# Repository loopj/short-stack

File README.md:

<div align="center">
  <h1>

  </h1>

  <h4>World's Smallest Nintendo Wii, using a trimmed motherboard and custom stacked PCBs</h4>

  <p>
    <a href="#features">Features</a> &middot;
    <a href="#size--scale">Size & Scale</a> &middot;
    <a href="#components">Components</a> &middot;
    <a href="#build-guide">Build Guide</a> &middot;
    <a href="#special-thanks">Special Thanks</a>
  </p>
</div>

## Features

- World's smallest "to scale" Wii console
- Powered by USB-C
- HDMI for lossless digital audio and video (powered by [GCVideo](https://github.com/ikorb/gcvideo))
- Bluetooth for Wii remotes and accessories
- MicroSD card stores games and saves, instead of disc drive & memory cards
- 4 GameCube controller ports
- Power, reset, and sync buttons
- Power indicator LED and iconic blue glowing disc slot
- Soft shutdown, power on/off via Wiimote

## Size & Scale

This is a **1:2.38 scale** model of an original Nintendo Wii console, but since that is hard to visualize here are some other stats:

- Same size as a typical deck of playing cards
- **7.4% the volume** of an original Wii console
- You could fit **13.5** of these inside an original Wii

I'm pretty sure this sets the record for the smallest functional scale-model Wii console, but let me know if I'm wrong!

### Could we go smaller?

Yes! It is definitely possible to go smaller than this. My [version of the Omega trim](images/trim.png) keeps all four main mounting holes, which makes it around 7mm wider than a classic Omega trim. Additionally [Wesk](https://twitter.com/Weskmods) has managed to get a Wii motherboard down to 52x52mm on his final destination trim, which is a a full 10mm narrower than my trim. I estimate you could reduce the volume by a further 25-30% without losing any functionality, but it would be an incredibly tight fit and tricky to assemble.

## Components

As the name implies, *Short Stack* is built from a stack of custom PCBs, and a custom heatsink, that are all designed to fit together in a compact and modular way.

### A modular motherboard

Making a tiny build like this is made possible by trimming the Wii motherboard down to the bare essentials. The result is a board which is just *62x62mm*, but still contains the CPU, GPU, RAM and flash memory.

Since we removed the original power circuitry and trimmed off the USB, Bluetooth, and GameCube connectors, we need to provide power and data to the board another way. I designed a couple of boards which solder directly to the front of a trimmed Wii motherboard to provide power and data, which help avoid a tangled mess of wires.

The [Wii Power Strip](https://github.com/loopj/wii-power-strip) supplies power to the Wii motherboards using a Molex Pico-Lock connector, and additionally has footprints to help relocate of a couple of capacitors which are typically removed when trimming a Wii.

[Periphlex](https://github.com/loopj/periphlex) is a flex PCB which breaks out the Bluetooth, USB and GameCube controller data lines, as well as the power, shutdown, and reset GPIOs. These are then made available via a 14-pin FFC connector. This approach replaces 11 magnet wires with a single, removable ribbon cable.

On the back of the motherboard, I'm using two open-source boards designed by the very talented [YveltalGriffin](https://github.com/mackieks). [fujiflex](https://github.com/mackieks/fujiflex) provides digital A/V output using GCVideo, and [nandFlex](https://github.com/mackieks/nandFlex) relocates the Wii's NAND memory chip, to enable the tight trim.

### Custom PCBs

In addition to the modular boards on the motherboard, I designed two PCBs specific to Short Stack which provide the rest of the functionality for the console.

The *main board* PCB hosts the power regulators, USB to microSD logic, HDMI connector, GameCube ports, and a microcontroller for power management. A 14-pin ribbon cable connects this board to the Wii motherboard via *Periphlex*, and a power cable delivers power to the *Power Strip*.

The *front panel* PCB hosts the power, reset, and sync buttons, as well as the power LED and disc slot LEDs. This board connects to the main board via a short 8-pin ribbon cable.

Since the GameCube controller connectors on the original Wii wouldn't fit cleanly on a build of this size, I use TRRS headphone connectors instead. This is the exact same approach used on the amazing [GC Nano](https://bitbuilt.net/forums/index.php?threads/gc-nano-the-worlds-smallest-gamecube.5697/) and in fact I made sure the dongles are pinout compatible!

### Cooling

The final part of the "stack" is a custom heatsink which is designed to be as low profile as possible, while still providing adequate cooling for the Wii's CPU and GPU. The heatsink is designed to be machined from aluminum or copper, and incorporates mounting holes which align with those on the Wii motherboard.

I managed to find a tiny 5V blower fan ([Pelonis AGB208N](https://catalog.pelonistechnologies.com/item/air-g-series-micro-fans-and-micro-blowers/micro-fans-and-micro-blowers/agb208n)) which measures just 20x20x8mm and somehow puts out 0.84 CFM of air. This blows air through the heatsink fins, out the side of the case.

### Case

The stack is housed in a custom 3D printed case, secured with four M2.5 screws and spacers. The rest of case is assembled using self-tapping M1.2 screws. The screw locations and fan vents are positioned to match the original Wii case as closely as possible, to minimize visible screws.

You can access files on the SD card by connecting the console to a computer via USB, but I also included an access panel on the front of the case where the original Wii SD card slot is found. This panel is held in place by magnets and can be removed to access the SD card without opening the case. Shout out to Wesk for the magnet idea!

To keep the clean aesthetic of the original Wii I wanted to hide the GameCube controller ports behind a panel. I always hated the hinged design of the original, and it is quite difficult to replicate at this scale, so I redesigned this panel to be a sliding panel.

The Wii's iconic disc slot lights are recreated using a 1.5mm thick custom cut acrylic light diffuser, which is illuminated by two side-mounted addressable LEDs on the front panel board. The power, reset, and sync buttons are all also 3D printed, and the power button hosts a tiny light pipe to allow the power LED to shine through.

I FDM printed the case on a Voron 2.4 in ABS using a 0.4mm nozzle at 0.1mm layer height, but it should print fine in PLA or PETG on a well-tuned printer. At this scale, dimensional accuracy is important. In theory it should be possible to print this on an SLA printer, but I haven't tried it.

## Build Guide

> [!CAUTION]
> This is not a beginner project! This build requires performing a challenging motherboard trim, fine pitch soldering, and PCB assembly. If you are not comfortable with these tasks, I would recommend starting with a simpler project and working your way up - check out the [BitBuilt forums](https://bitbuilt.net) for some awesome project worklogs.

### What you'll need

- 4-layer Wii motherboard
- [nandFlex](https://github.com/mackieks/nandFlex) board (or [4Layer Technologies RVL-NAND](https://4layertech.com/products/rvl-nand-flex-board-pack-of-2))
- Assembled [fujiflex](https://github.com/mackieks/fujiflex) (or [ElectronAVE](https://electron-shepherd.com/products/electronave-kit))
- Assembled [Wii Power Strip](https://github.com/loopj/wii-power-strip/tree/r1) - **must be revision 1!**
- Assembled [Periphlex](https://github.com/loopj/periphlex)
- [Short Stack main board](main-board/KiCad) - 1.2mm thickness, stencil recommended
- [Short Stack front panel](front-panel/KiCad) - 0.8mm thickness, black soldermask, stencil recommended
- [Heatsink](case/heatsink.step) - machined from aluminum or copper
- [Light diffuser](case/disc-light-diffuser.dxf) - cut from 1.5mm thick acrylic
- The components and hardware from the [bill of materials](full-bom.xlsx)

### Assembly

- Assemble main board and front panel PCBs
  - I recommend using a solder stencil and a hot plate or reflow oven
  - If using a hot plate, hand solder the headphone connectors after reflowing the rest of the components
  - Secure two 3 x 1mm magnets inside the holes on the front panel board using a dab of CA glue
- Flash the [main board firmware](main-board/firmware)
- Prepare and trim the Wii motherboard
  - Relocate the NAND, test it still boots
  - Perform a wireless U10 relocation, test it still boots - you may wish to wire a magnet wire to the [`SHUTDOWN` via](https://bitbuilt.net/forums/index.php?threads/soft-shutdown-power-on-via-bluetooth.6239/) first
  - Install fujiflex, and test digital A/V output works
  - Trim the motherboard (see [trim dimensions](images/trim.png))
- Assemble and install *Power Strip* ([see instructions](https://github.com/loopj/wii-power-strip/tree/r1#installation))
- Assemble and install *Periphlex* ([see instructions](https://github.com/loopj/periphlex#installation))
- Connect the boards
  - Connect the main board to the motherboard via a 14-pin FFC cable to *Periphlex*
  - Connect the main board to the motherboard via a 5-pin Molex Pico-Lock cable to *Power Strip*
  - Connect the front panel board to the main board via an 8-pin FFC cable
  - Connect the fan to the main board
  - Apply thermal paste to the CPU and GPU
  - Stack the components: heatsink, motherboard, M2.5 x 3mm spacers, main board
  - Install the stack to the case bottom using M2.5 x 12mm wafer head screws
- Secure the top of the case to the bottom using four M1.2 x 4mm screws
- Secure the front panel PCB to the front of the case using two M1.2 x 3mm screws
- Secure the front of the case to the bottom of the case using two M1.2 x 4mm screws
- Press-fit two 3 x 1mm magnets into the holes on the sd card cover, make sure they match polarity with the magnets on the front panel PCB
- Slide the side panel into the case

## Special Thanks

This project would not be possible without the amazing [BitBuilt community](https://bitbuilt.net), I'm truly standing on the shoulders of giants here.

In particular, I'd like to thank:

- [Wesk](https://twitter.com/Weskmods) for setting the bar so high with renders, for the suggestion of using magnets in the case assembly, and for the inspirational GC Nano
- [Aurelio](https://twitter.com/aureliomannara) for pointing me in the right direction to help figure the soft shutdown and power on via Wiimote.
- [YveltalGriffin](https://twitter.com/YveltalGriffin) for PCB design feedback, helping me when I was documenting the bluetooth module, and of course for fujiflex and nandFlex
- [CrazyGadget](https://twitter.com/crazygadgetmods) for helping me fix my GL823K on the first revision of my boards, and for the inspirational GC Nano
- [Y2K](https://twitter.com/y2k_x38) and supertazon for joining the PCB assembly live stream and being super supportive

## License

Permissively released under the Solderpad Hardware License v2.1

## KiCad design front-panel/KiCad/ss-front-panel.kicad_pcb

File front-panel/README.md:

# Short Stack Front Panel

This folder contains the KiCad schematic and PCB layout for the Short Stack front panel PCB.

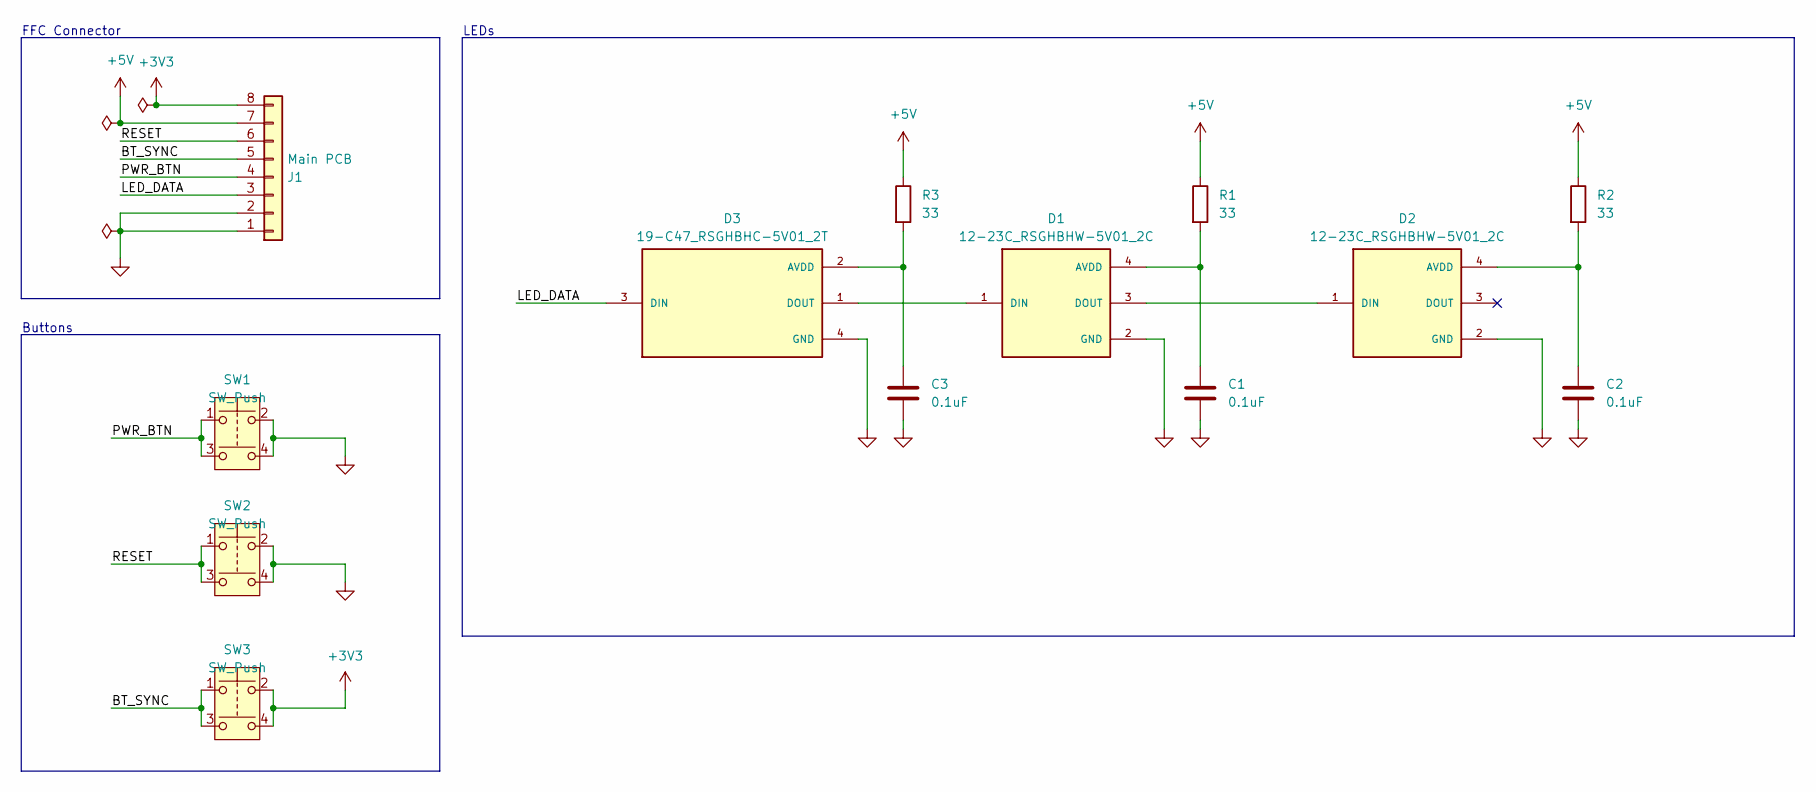
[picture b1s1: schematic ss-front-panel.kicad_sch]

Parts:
C1, C2, C3: 0.1uF; C_0402_1005Metric
D1, D2: 12-23C_RSGHBHW-5V01_2C; LED_12-23C_RSGHBHW-5V01_2C; MPN 12-23C/RSGHBHW-5V01/2C; Digi-Key Part # 1080-1624-1-ND
D3: 19-C47_RSGHBHC-5V01_2T; LED_19-C47_RSGHBHC-5V01_2T; MPN 19-C47/RSGHBHC-5V01/2T; Digi-Key Part # 1080-1623-1-ND
J1: Main PCB; 5034800800; MPN 5014610891; Digi-Key Part # WM14413CT-ND
R1, R2, R3: 33; R_0402_1005Metric
SW1, SW2, SW3: SW_Push; R668048; MPN R-668048; Digi-Key Part # 2508-R-668048CT-ND

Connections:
+3V3: J1.8, SW3.2, SW3.4
+5V: J1.7, R1.1, R2.1, R3.1
/BT_SYNC: J1.5, SW3.1, SW3.3
/LED_DATA: D3.3 (DIN), J1.3
/PWR_BTN: J1.4, SW1.1, SW1.3
/RESET: J1.6, SW2.1, SW2.3
GND: C1.2, C2.2, C3.2, D1.2 (GND), D2.2 (GND), D3.4 (GND), J1.1, J1.2, SW1.2, SW1.4, SW2.2, SW2.4
unnamed: C1.1, D1.4 (AVDD), R1.2
unnamed: D1.1 (DIN), D3.1 (DOUT)
unnamed: D1.3 (DOUT), D2.1 (DIN)
unnamed: C2.1, D2.4 (AVDD), R2.2
unnamed: C3.1, D3.2 (AVDD), R3.2

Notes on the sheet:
FFC Connector
Buttons
LEDs

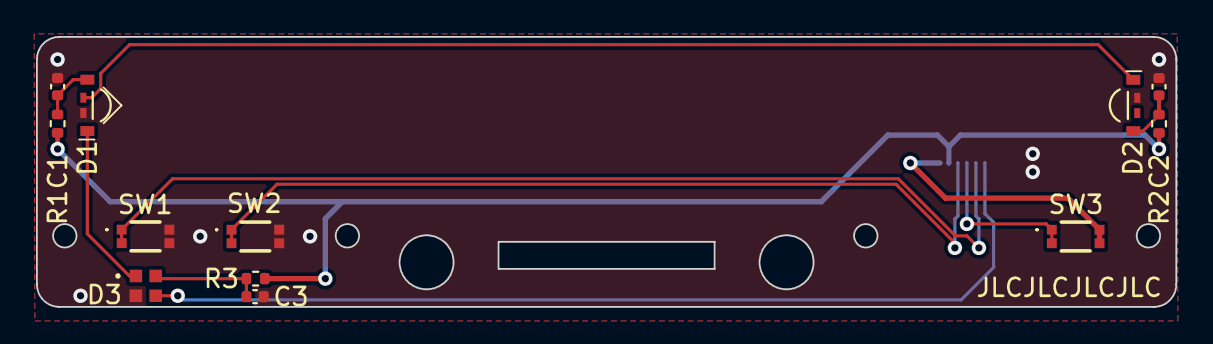
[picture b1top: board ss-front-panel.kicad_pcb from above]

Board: 2 copper layers, 63.3 x 15.0 mm, 13 parts (1 on the bottom side), 12 nets.

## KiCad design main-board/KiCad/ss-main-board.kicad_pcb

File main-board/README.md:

# Short Stack Main Board

The folder contains the KiCad schematic, pcb layouts, and firmware for the Short Stack main PCB.

## Future enhancements

- [ ] Dual load switch per GC line to allow hotplug (TPS22960 or similar)
- [ ] Potentially drop the 5V load switch if we are load switching each GC controller
- [ ] Hang bluetooth antenna off right edge of board

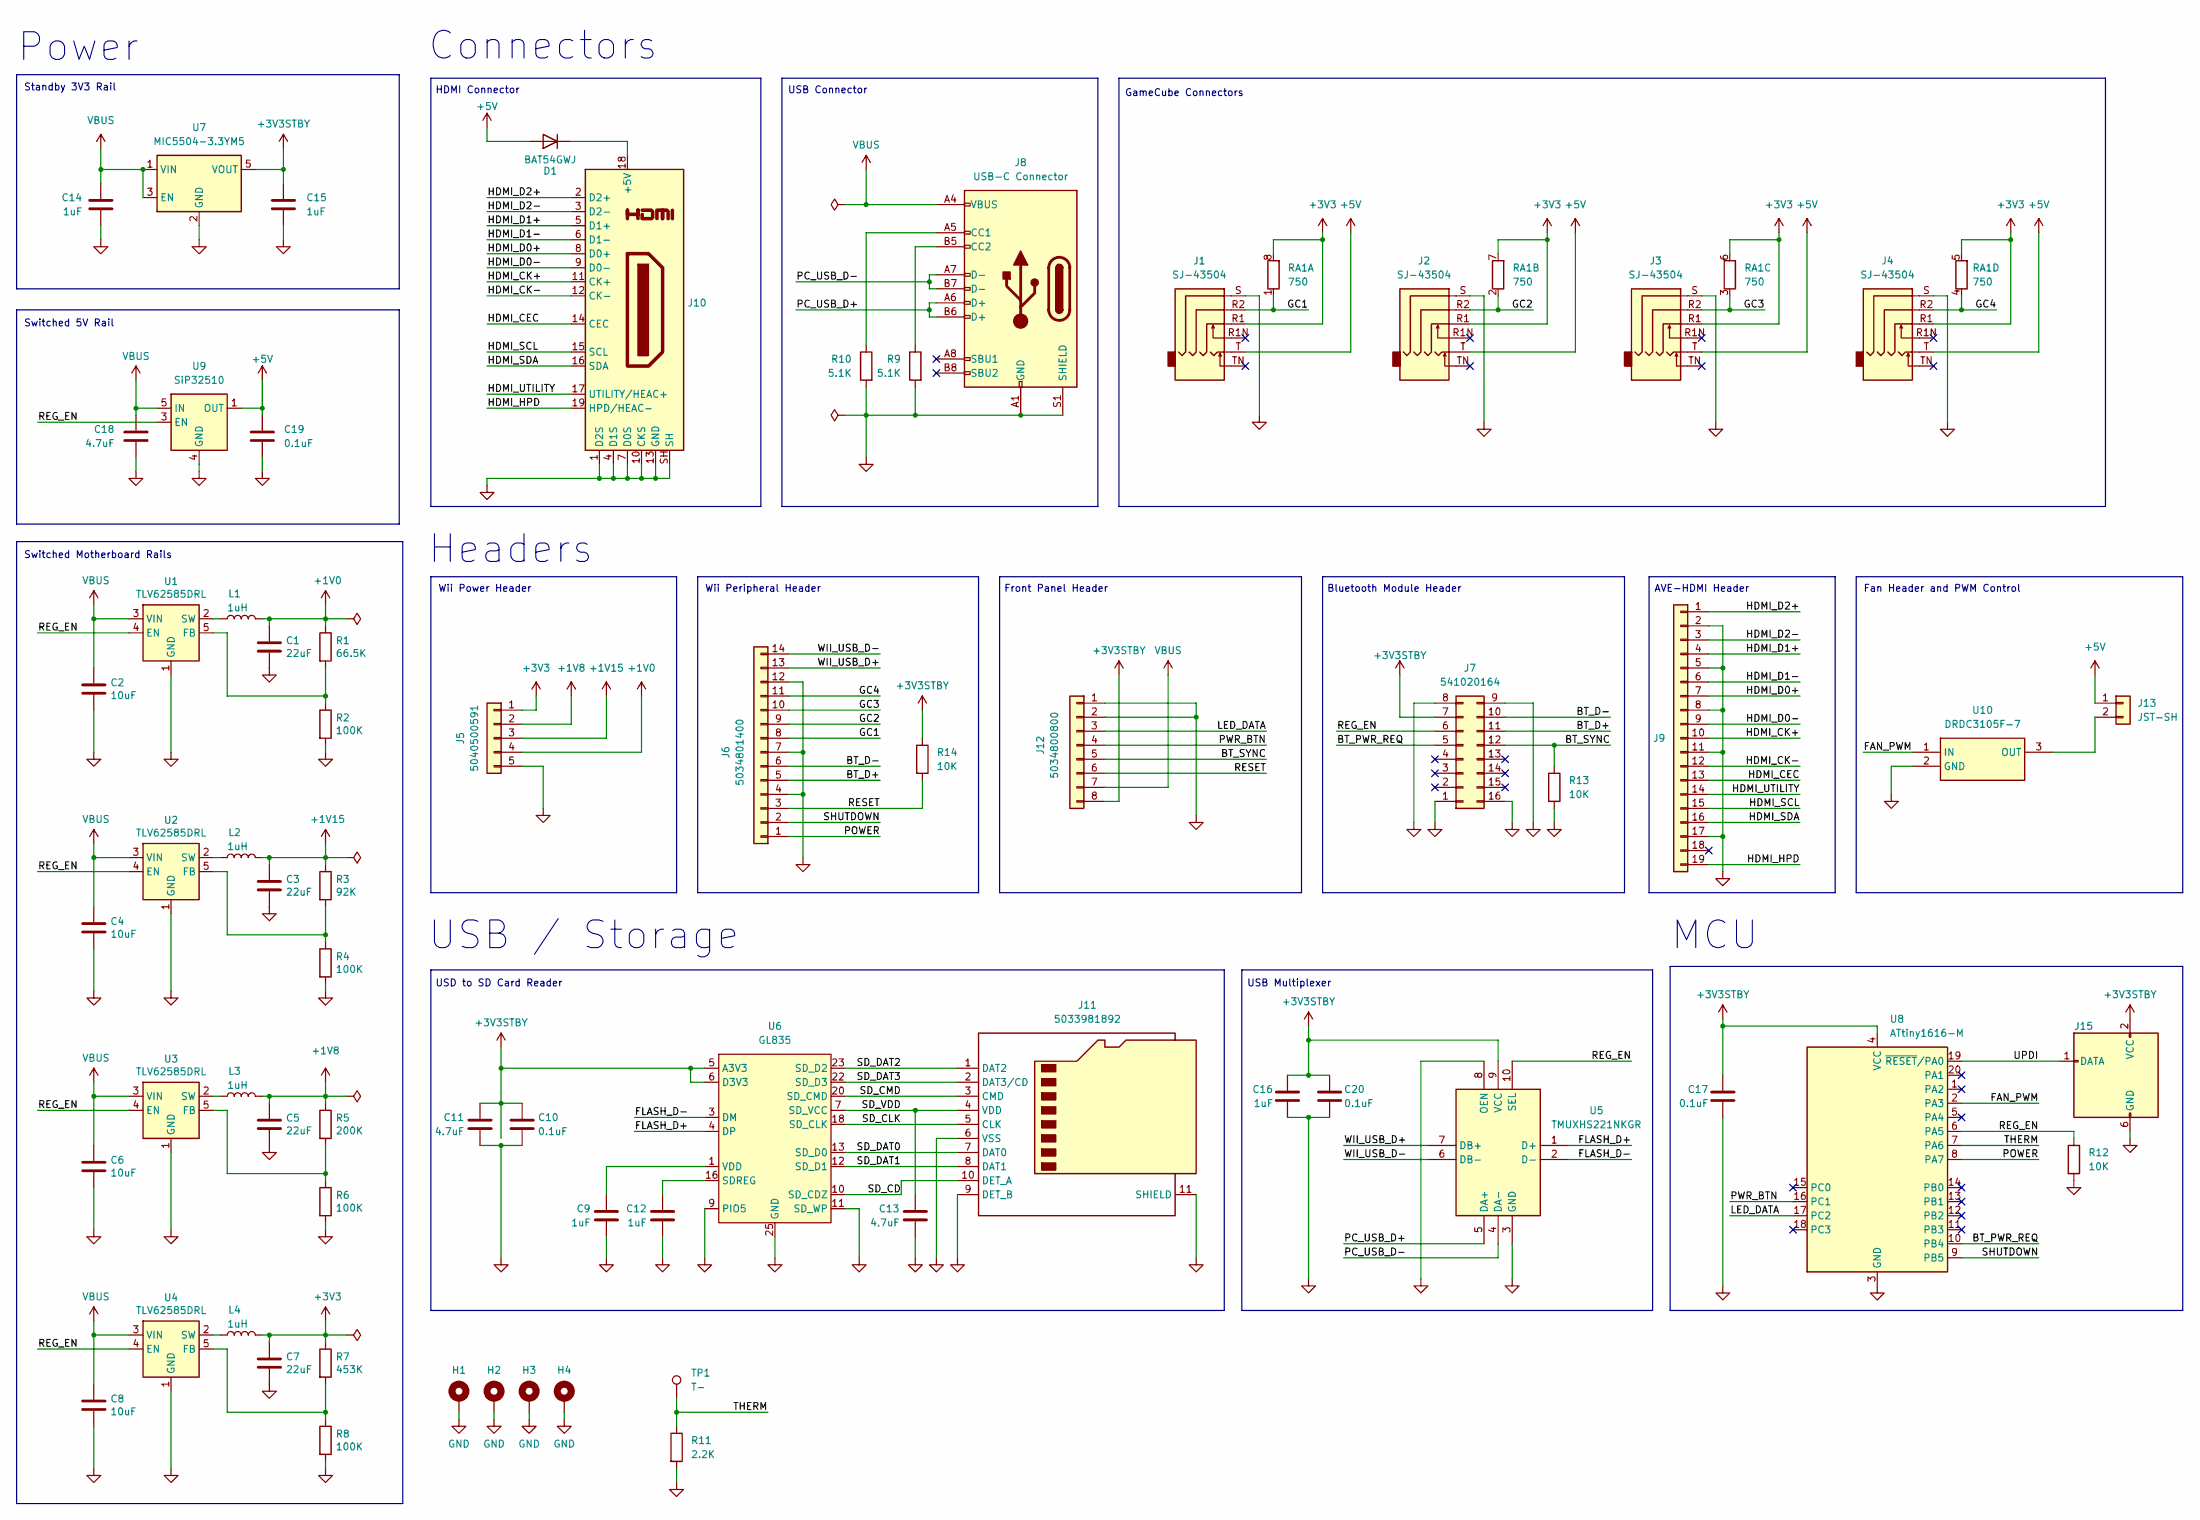
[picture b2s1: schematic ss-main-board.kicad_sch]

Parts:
C1, C3, C5, C7: 22uF; C_0805_2012Metric
C2, C4, C6, C8: 10uF; C_0805_2012Metric
C9, C12, C14, C15, C16: 1uF; C_0402_1005Metric
C10, C17, C19, C20: 0.1uF; C_0402_1005Metric
C11, C13, C18: 4.7uF; C_0402_1005Metric
D1: BAT54GWJ; D_SOD-123
H1, H2, H3, H4: MountingHole_Pad; MountingHole_2.7mm_M2.5_ISO7380_Pad_TopBottom
J1, J2, J3, J4: SJ-43504; SJ-43504-SMT-TR; MPN SJ-43504-SMT-TR; Digi-Key Part # CP-43504SJCT-ND
J5: 5040500591; MPN 5040500591; Digi-Key Part # WM24877CT-ND
J6: 5034801400; MPN 5034801200; Digi-Key Part # WM1441CT-ND
J7: 541020164; Wii_Bluetooth_Module; MPN 0541020164; Digi-Key Part # WM8876CT-ND
J8: USB-C Connector; MOLEX_2171790001; MPN 217179-0001; Digi-Key Part # 900-2171790001CT-ND
J9: AVE-HDMI Connector; 5052781933; MPN 5052781933; Digi-Key Part # 900-5052781933CT-ND
J10: HDMI_C_1.4; 20139781; MPN 2013978-1; Digi-Key Part # A107963CT-ND
J11: 5033981892; 503398-1892
J12: 5034800800; MPN 5014610812; Digi-Key Part # WM9076CT-ND
J13: JST-SH; JST_SH_SM02B-SRSS-TB_1x02-1MP_P1.00mm_Horizontal; MPN SM02B-SRSS-TB; Digi-Key Part # 455-SM02B-SRSS-TBCT-ND
J15: AVR-UPDI-6; UPDI Pads
L1, L2, L3, L4: 1uH; L_Vishay_IHLP-1212; MPN IHLP1212BZER1R0M11; Digi-Key Part # 541-1319-1-ND
R1: 66.5K; R_0402_1005Metric
R2, R4, R6, R8: 100K; R_0402_1005Metric
R3: 92K; R_0402_1005Metric
R5: 200K; R_0402_1005Metric
R7: 453K; R_0402_1005Metric
R9, R10: 5.1K; R_0402_1005Metric
R11: 2.2K; R_0402_1005Metric
R12, R13, R14: 10K; R_0402_1005Metric
RA1: 750; R_Array_Concave_4x0603
TP1: T-; TestPoint_Pad_D1.0mm
U1, U2, U3, U4: TLV62585DRL; SOTFL50P160X60-6N; MPN TLV62585DRLR; Digi-Key Part # 296-51694-1-ND
U5: TMUXHS221NKGR; Manufacturer_Part_Number TMUXHS221NKGR; Mouser Part Number 595-TMUXHS221NKGR
U6: GL835; QFN-24-1EP_4x4mm_P0.5mm_EP2.6x2.6mm
U7: MIC5504-3.3YM5; SOT-23-5; MPN MIC5504-3.3YM5-TR; Digi-Key Part # 576-4764-1-ND
U8: ATtiny1616-M; VQFN-20-1EP_3x3mm_P0.4mm_EP1.7x1.7mm
U9: SiP32510; TSOT-23-6
U10: DRDC3105F-7; SOT-23; Manufacturer_Part_Number DRDC3105F-7; Mouser Part Number 621-DRDC3105F-7

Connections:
+1V0: C1.1, J5.4, L1.2, R1.1
+1V8: C5.1, J5.2, L3.2, R5.1
+1V15: C3.1, J5.3, L2.2, R3.1
+3V3: C7.1, J1.R1, J2.R1, J3.R1, J4.R1, J5.1, L4.2, R7.1, RA1.5 (R4.2), RA1.6 (R3.2), RA1.7 (R2.2), RA1.8 (R1.2)
+3V3STBY: C10.1, C11.1, C15.1, C16.1, C17.1, C20.1, J7.7, J12.8, J15.2 (VCC), R14.1, U5.9 (VCC), U6.5 (A3V3), U6.6 (D3V3), U7.5 (VOUT), U8.4 (VCC)
+5V: C19.1, D1.2 (A), J1.T, J2.T, J3.T, J4.T, J13.1, U9.1 (OUT), U9.2 (OUT)
/BT_D+: J6.5, J7.11
/BT_D-: J6.6, J7.10
/BT_PWR_REQ: J7.5, U8.10 (PB4)
/BT_SYNC: J7.12, J12.5, R13.1
/FAN_PWM: U8.2 (PA3), U10.1 (IN)
/FLASH_D+: U5.1 (D+), U6.4 (DP)
/FLASH_D-: U5.2 (D-), U6.3 (DM)
/GC1: J1.R2, J6.8, RA1.1 (R1.1)
/GC2: J2.R2, J6.9, RA1.2 (R2.1)
/GC3: J3.R2, J6.10, RA1.3 (R3.1)
/GC4: J4.R2, J6.11, RA1.4 (R4.1)
/HDMI_CEC: J9.13, J10.14 (CEC)
/HDMI_CK+: J9.10, J10.11 (CK+)
/HDMI_CK-: J9.12, J10.12 (CK-)
/HDMI_D0+: J9.7, J10.8 (D0+)
/HDMI_D0-: J9.9, J10.9 (D0-)
/HDMI_D1+: J9.4, J10.5 (D1+)
/HDMI_D1-: J9.6, J10.6 (D1-)
/HDMI_D2+: J9.1, J10.2 (D2+)
/HDMI_D2-: J9.3, J10.3 (D2-)
/HDMI_HPD: J9.19, J10.19 (HPD/HEAC-)
/HDMI_SCL: J9.15, J10.15 (SCL)
/HDMI_SDA: J9.16, J10.16 (SDA)
/HDMI_UTILITY: J9.14, J10.17 (UTILITY/HEAC+)
/LED_DATA: J12.3, U8.17 (PC2)
/PC_USB_D+: J8.A6 (D+), J8.B6 (D+), U5.5 (DA+)
/PC_USB_D-: J8.A7 (D-), J8.B7 (D-), U5.4 (DA-)
/POWER: J6.1, U8.8 (PA7)
/PWR_BTN: J12.4, U8.16 (PC1)
/REG_EN: J7.6, R12.1, U1.4 (EN), U2.4 (EN), U3.4 (EN), U4.4 (EN), U5.10 (SEL), U8.6 (PA5), U9.3 (EN)
/RESET: J6.3, J12.6, R14.2
/SD_CD: J11.10 (DET_A), U6.10 (SD_CDZ)
/SD_CLK: J11.5 (CLK), U6.18 (SD_CLK)
/SD_CMD: J11.3 (CMD), U6.20 (SD_CMD)
/SD_DAT0: J11.7 (DAT0), U6.13 (SD_D0)
/SD_DAT1: J11.8 (DAT1), U6.12 (SD_D1)
/SD_DAT2: J11.1 (DAT2), U6.23 (SD_D2)
/SD_DAT3: J11.2 (DAT3/CD), U6.22 (SD_D3)
/SD_VDD: C13.1, J11.4 (VDD), U6.7 (SD_VCC)
/SHUTDOWN: J6.2, U8.9 (PB5)
/THERM: R11.1, TP1.1, U8.7 (PA6)
/UPDI: J15.1 (DATA), U8.19 (~RESET/PA0)
/WII_USB_D+: J6.13, U5.7 (DB+)
/WII_USB_D-: J6.14, U5.6 (DB-)
GND: C1.2, C2.2, C3.2, C4.2, C5.2, C6.2, C7.2, C8.2, C9.2, C10.2, C11.2, C12.2, C13.2, C14.2, C15.2, C16.2, C17.2, C18.2, C19.2, C20.2, H1.1, H2.1, H3.1, H4.1, J1.S, J2.S, J3.S, J4.S, J5.5, J6.4, J6.7, J6.12, J7.1, J7.8, J7.9, J7.16, J8.A1 (GND), J8.A12 (GND), J8.B1 (GND), J8.B12 (GND), J8.S1 (SHIELD), J9.2, J9.5, J9.8, J9.11, J9.17, J10.1 (D2S), J10.4 (D1S), J10.7 (D0S), J10.10 (CKS), J10.13 (GND), J10.SH, J11.6 (VSS), J11.9 (DET_B), J11.11 (SHIELD), J12.1, J12.2, J15.6 (GND), R2.2, R4.2, R6.2, R8.2, R9.2, R10.2, R11.2, R12.2, R13.2, U1.1 (GND), U2.1 (GND), U3.1 (GND), U4.1 (GND), U5.3 (GND), U5.8 (OEN), U6.9 (PIO5), U6.11 (SD_WP), U6.25 (GND), U7.2 (GND), U8.3 (GND), U8.21 (GND), U9.4 (GND), U10.2 (GND)
unnamed: D1.1 (K), J10.18 (+5V)
unnamed: J8.A5 (CC1), R10.1
unnamed: J8.B5 (CC2), R9.1
unnamed: J13.2, U10.3 (OUT)
unnamed: R1.2, R2.1, U1.5 (FB)
unnamed: L1.1, U1.2 (SW)
unnamed: R3.2, R4.1, U2.5 (FB)
unnamed: L2.1, U2.2 (SW)
unnamed: R5.2, R6.1, U3.5 (FB)
unnamed: L3.1, U3.2 (SW)
unnamed: R7.2, R8.1, U4.5 (FB)
unnamed: L4.1, U4.2 (SW)
unnamed: C12.1, U6.16 (SDREG)
unnamed: C9.1, U6.1 (VDD)
VBUS: C2.1, C4.1, C6.1, C8.1, C14.1, C18.1, J8.A4 (VBUS), J8.A9 (VBUS), J8.B4 (VBUS), J8.B9 (VBUS), J12.7, U1.3 (VIN), U2.3 (VIN), U3.3 (VIN), U4.3 (VIN), U7.1 (VIN), U7.3 (EN), U9.5 (IN), U9.6 (IN)

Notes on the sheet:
Wii Power Header
USB Multiplexer
HDMI Connector
AVE-HDMI Header
Power
Front Panel Header
Wii Peripheral Header
Standby 3V3 Rail
Connectors
USD to SD Card Reader
Bluetooth Module Header
Headers
GameCube Connectors
USB Connector
Fan Header and PWM Control
Switched 5V Rail
MCU
USB / Storage
Switched Motherboard Rails

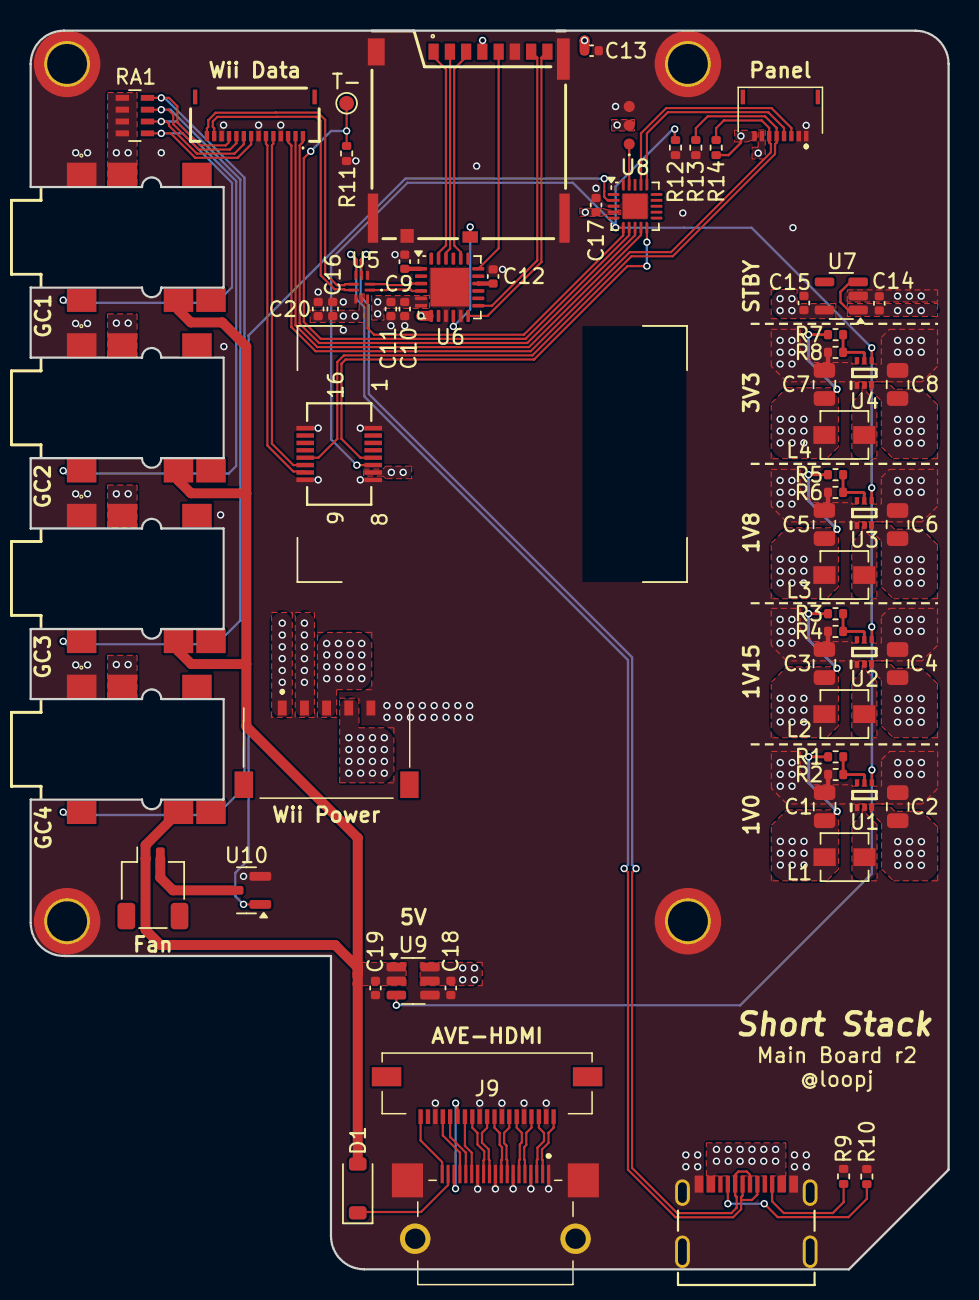
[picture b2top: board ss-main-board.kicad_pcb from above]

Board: 4 copper layers, 62.1 x 83.8 mm, 69 parts (0 on the bottom side), 66 nets.

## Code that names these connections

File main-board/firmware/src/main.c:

#include <avr/interrupt.h>
#include <avr/io.h>
#include <stdbool.h>

#include "events.h"
#include "gpio.h"
#include "led.h"
#include "rtc.h"

// GPIO definitions
static const gpio_t FAN_PWM    = {&PORTA, 3};
static const gpio_t REG_EN     = {&PORTA, 5};
static const gpio_t THERM      = {&PORTA, 6};
static const gpio_t POWER      = {&PORTA, 7};
static const gpio_t BT_PWR_REQ = {&PORTB, 4};
static const gpio_t SHUTDOWN   = {&PORTB, 5};
static const gpio_t PWR_BTN    = {&PORTC, 1};

// LED definitions
static const uint8_t POWER_LED  = 0;
static const uint8_t DISC_LED_L = 1;
static const uint8_t DISC_LED_R = 2;

// Output pulse timings
static const uint16_t POWER_PULSE_MS = 30;

// Button press thresholds
static const uint16_t BTN_PRESS_MS = 10;
static const uint16_t BTN_HOLD_MS  = 2000;

// Button states
enum button_state { BUTTON_RELEASED, BUTTON_PRESSED, BUTTON_HELD };

// Flags for events detected in interrupt handlers
enum event_flags { PWR_BTN_PRESS_EVENT, PWR_BTN_HOLD_EVENT, BT_PWR_REQ_EVENT, SHUTDOWN_EVENT };

// State
bool regs_enabled          = false;
bool power_pulse_active    = false;
uint32_t power_pulse_start = 0;

// Enable or disable the main regulators, updating the LEDs accordingly
void set_regulator_state(bool enabled)
{
    if (enabled) {
        // Turn on main regulators
        gpio_set_high(REG_EN);

        // Turn on the fan
        gpio_set_high(FAN_PWM);

        // Set power indicator LED to green, disc LEDs to cyan
        led_set_color(POWER_LED, 0x002000);
        led_set_color(DISC_LED_L, 0x00FFFF);
        led_set_color(DISC_LED_R, 0x00FFFF);
    } else {
        // Turn off main regulators
        gpio_set_low(REG_EN);

        // Turn off the fan
        gpio_set_low(FAN_PWM);

        // Set power indicator LED to red, turn off disc LEDs
        led_set_color(POWER_LED, 0x200000);
        led_set_color(DISC_LED_L, 0x000000);
        led_set_color(DISC_LED_R, 0x000000);
    }

    // Refresh the LEDs
    led_refresh();

    // Update state
    regs_enabled = enabled;
}

// Update the state of the power button
void update_pwr_btn_events()
{
    static bool last_gpio_state           = true;
    static uint32_t last_millis           = 0;
    static enum button_state button_state = BUTTON_RELEASED;

    // Read the current state of the power button (active low)
    bool gpio_state = gpio_read(PWR_BTN);

    // Reset hold time and flags if the button state has changed
    uint32_t millis = rtc_millis();
    if (gpio_state != last_gpio_state) {
        last_millis  = millis;
        button_state = BUTTON_RELEASED;
    }

    // If the button is down, check for hold time thresholds
    if (gpio_state == false) {
        // Raise event flags when hold time thresholds are reached
        if (millis - last_millis >= BTN_PRESS_MS && button_state < BUTTON_PRESSED) {
            button_state = BUTTON_PRESSED;
            event_set(PWR_BTN_PRESS_EVENT);
        } else if (millis - last_millis >= BTN_HOLD_MS && button_state < BUTTON_HELD) {
            button_state = BUTTON_HELD;
            event_set(PWR_BTN_HOLD_EVENT);
        }
    }

    // Save the current state for comparison next time
    last_gpio_state = gpio_state;
}

// Send a pulse to the POWER GPIO to request a soft shutdown
void send_power_pulse()
{
    gpio_set_high(POWER);
    power_pulse_active = true;
    power_pulse_start  = rtc_millis();
}

// Clear the POWER GPIO if the pulse has been active for the required time
void clear_completed_power_pulse()
{
    if (power_pulse_active && rtc_millis() - power_pulse_start >= POWER_PULSE_MS) {
        gpio_set_low(POWER);
        power_pulse_active = false;
    }
}

// Disable the prescaler to run the CPU at full speed
void clk_disable_prescaler()
{
    CPU_CCP = CCP_IOREG_gc;
    CLKCTRL.MCLKCTRLB &= ~CLKCTRL_PEN_bm;
}

// Initialize the GPIOs
void gpio_init()
{
    // Power button input (active low on button press)
    gpio_input(PWR_BTN);
    gpio_config(PWR_BTN, PORT_PULLUPEN_bm);

    // Bluetooth power request input (active high, ~110ms pulse)
    gpio_input(BT_PWR_REQ);
    gpio_config(BT_PWR_REQ, PORT_ISC_RISING_gc);

    // Soft shutdown complete input (active high, ~120ms pulse)
    gpio_input(SHUTDOWN);
    gpio_config(SHUTDOWN, PORT_ISC_RISING_gc);

    // Regulator enable output
    gpio_output(REG_EN);

    // Soft shutdown request output
    gpio_output(POWER);

    // Fan power output
    gpio_output(FAN_PWM);
}

// Handle external interrupts on PORTB
ISR(PORTB_PORT_vect)
{
    // Check for "bluetooth power request" pulse
    if (gpio_read_intflag(BT_PWR_REQ)) {
        event_set(BT_PWR_REQ_EVENT);
    }

    // Check for "soft shutdown complete" pulse
    if (gpio_read_intflag(SHUTDOWN)) {
        event_set(SHUTDOWN_EVENT);
    }

    // Clear the interrupt flags
    PORTB.INTFLAGS = 0xFF;
}

int main()
{
    // Initialize the RTC with a 1ms periodic interrupt
    // We need this to measure power button press and hold times, and to time output pulses
    rtc_init();

    // Initialize the GPIOs
    gpio_init();

    // Initialize the addressable LEDs
    led_init();

    // Disable the prescaler to run the CPU at full speed
    // Required for accurate bit-banging of LEDs
    clk_disable_prescaler();

    // Enable global interrupts
    sei();

    // Set the initial state of the main regulators to off
    set_regulator_state(false);

    // Main loop
    while (true) {
        // Check for power button events (press, hold)
        update_pwr_btn_events();

        // Check for completed power pulses, and turn off the POWER gpio if necessary
        clear_completed_power_pulse();

        // Handle power button presses
        if (event_get(PWR_BTN_PRESS_EVENT)) {
            if (regs_enabled) {
                // Send a soft shutdown request pulse to Hollywood
                send_power_pulse();
            } else {
                // Turn on the main regulators if they are off
                set_regulator_state(true);
            }
        }

        // Turn off the main regulators if the power button is held for 2 seconds
        if (event_get(PWR_BTN_HOLD_EVENT)) {
            if (regs_enabled)
                set_regulator_state(false);
        }

        // Handle bluetooth power request pulses
        if (event_get(BT_PWR_REQ_EVENT)) {
            if (regs_enabled) {
                // Send a soft shutdown request pulse to Hollywood
                send_power_pulse();
            } else {
                // Turn on the main regulators if they are off
                set_regulator_state(true);
            }
        }

        // Turn off the main regulators if Hollywood indicates a soft shutdown is complete
        if (event_get(SHUTDOWN_EVENT)) {
            if (regs_enabled)
                set_regulator_state(false);
        }
    }

    return 0;
}

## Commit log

2024-04-18 Fix case side step file
2024-04-18 Add comparison image to stock wii
2024-04-18 Fix typo
2024-04-18 Add missing button cad file
2025-03-31 Add missing 19-pin hdmi ffc to BOM
2025-10-23 Add ibom
